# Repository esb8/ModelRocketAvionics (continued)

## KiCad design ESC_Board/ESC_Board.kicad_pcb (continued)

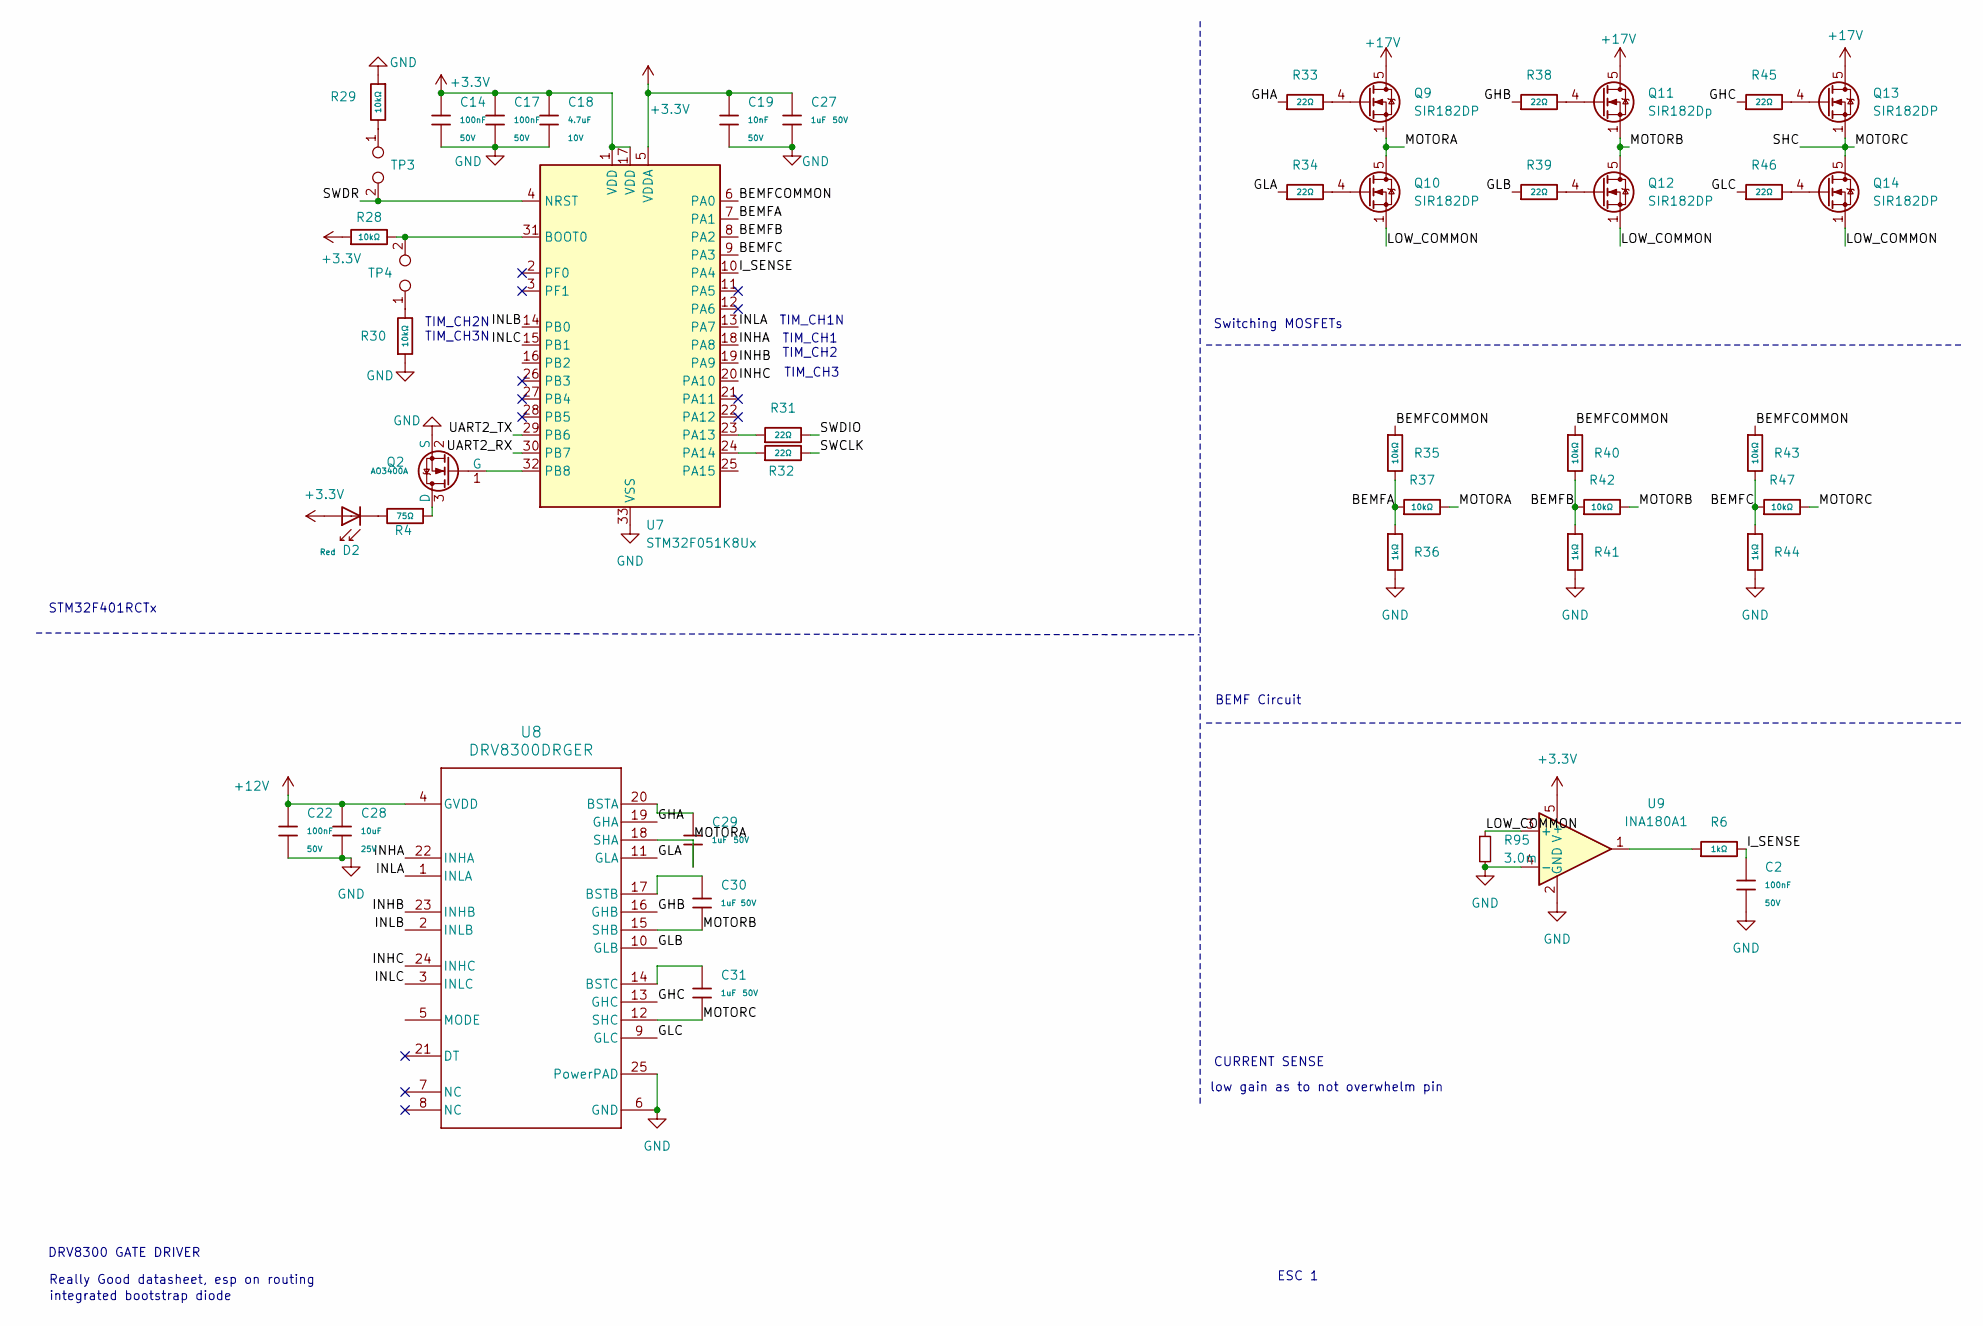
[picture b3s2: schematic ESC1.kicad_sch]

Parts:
C2, C14, C17, C22: 100nF; C_0402; Voltage Rated 50V; Tolerance ±10%; Part CL05B104KB54PNC; LCSC C307331
C18: 4.7uF; C_0402; Voltage Rated 10V; Tolerance ±20%; Part CL05A475MP5NRNC; LCSC C23733
C19: 10nF; C_0402; Voltage Rated 50V; Tolerance ±10%; Part CL05B103KB5NNNC; LCSC C15195
C27, C29, C30, C31: 1uF; C_0603; Voltage Rated 50V; Tolerance ±10%; LCSC C6119857
C28: 10uF; C_0603; Voltage Rated 25V; Tolerance ±20%; Part CL10A106MA8NRNC; LCSC C96446
D2: Red; D_0805; Forward Voltage (VF) 1.6V~2.6V; Part NCD0805R1; LCSC C84256
Q2: AO3400A; Q_SOT-23; Part AO3400A; LCSC C20917
Q9, Q10, Q12, Q13, Q14: SIR182DP; TDSON-8-1; LCSC C151507
Q11: SIR182Dp; TDSON-8-1; LCSC C151507
R4: 75Ω; R_0402; Tolerance ±1%; Part 0402WGF750JTCE; LCSC C4275
R6, R36, R41, R44: 1kΩ; R_0402; Tolerance ±1%; Part HP02WAJ0102TCE; LCSC C2759467
R28, R29, R30, R35, R37, R40, R42, R43, R47: 10kΩ; R_0402; Tolerance ±1%; LCSC C191123
R31, R32, R33, R34, R38, R39, R45, R46: 22Ω; R_0402; Tolerance ±1%; LCSC C400511
R95: 3.0m; R_2512_6332Metric; LCSC C2994640
TP3, TP4: TestPoint_2Pole
U7: STM32F051K8Ux; QFN-32-1EP_5x5mm_P0.5mm_EP3.45x3.45mm
U8: DRV8300DRGER; RGE0024B-IPC_A
U9: INA180A1; SOT-23-5

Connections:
+3.3V: C14.1, C17.1, C18.1, C19.1, C27.1, D2.2, R28.1, U7.1 (VDD), U7.5 (VDDA), U7.17 (VDD), U9.5 (V+); also elsewhere on the board
+12V: C22.1, C28.2, U8.4 (GVDD); also elsewhere on the board
+17V: Q9.5 (D), Q11.5 (D), Q13.5 (D); also elsewhere on the board
/ESC2.sch/BEMFA: R35.2, R36.1, R37.1, U7.7 (PA1)
/ESC2.sch/BEMFB: R40.2, R41.1, R42.1, U7.8 (PA2)
/ESC2.sch/BEMFC: R43.2, R44.1, R47.1, U7.9 (PA3)
/ESC2.sch/BEMFCOMMON: R35.1, R40.1, R43.1, U7.6 (PA0)
/ESC2.sch/GHA: R33.1, U8.19 (GHA)
/ESC2.sch/GHB: R38.1, U8.16 (GHB)
/ESC2.sch/GHC: R45.1, U8.13 (GHC)
/ESC2.sch/GLA: R34.1, U8.11 (GLA)
/ESC2.sch/GLB: R39.1, U8.10 (GLB)
/ESC2.sch/GLC: R46.1, U8.9 (GLC)
/ESC2.sch/INHA: U7.18 (PA8), U8.22 (INHA)
/ESC2.sch/INHB: U7.19 (PA9), U8.23 (INHB)
/ESC2.sch/INHC: U7.20 (PA10), U8.24 (INHC)
/ESC2.sch/INLA: U7.13 (PA7), U8.1 (INLA)
/ESC2.sch/INLB: U7.14 (PB0), U8.2 (INLB)
/ESC2.sch/INLC: U7.15 (PB1), U8.3 (INLC)
/ESC2.sch/I_SENSE: C2.1, R6.2, U7.10 (PA4)
/ESC2.sch/LOW_COMMON: Q10.1 (S), Q10.2 (S), Q10.3 (S), Q12.1 (S), Q12.2 (S), Q12.3 (S), Q14.1 (S), Q14.2 (S), Q14.3 (S), R95.1, U9.3 (+)
/ESC2.sch/MOTORA: C29.2, Q9.1 (S), Q9.2 (S), Q9.3 (S), Q10.5 (D), R37.2, U8.18 (SHA)
/ESC2.sch/MOTORB: C30.2, Q11.1 (S), Q11.2 (S), Q11.3 (S), Q12.5 (D), R42.2, U8.15 (SHB)
/ESC2.sch/MOTORC: C31.2, Q13.1 (S), Q13.2 (S), Q13.3 (S), Q14.5 (D), R47.2, U8.12 (SHC)
/ESC2.sch/SWCLK: R32.2
/ESC2.sch/SWDIO: R31.2
/ESC2.sch/SWDR: U7.4 (NRST)
/ESC2.sch/UART2_RX: U7.30 (PB7)
/ESC2.sch/UART2_TX: U7.29 (PB6)
GND: C2.2, C14.2, C17.2, C18.2, C19.2, C22.2, C27.2, C28.1, Q2.2 (S), R29.1, R30.1, R36.2, R41.2, R44.2, R95.2, U7.33 (VSS), U8.6 (GND), U8.25 (PowerPAD), U9.2 (GND), U9.4 (-); also elsewhere on the board
unnamed: D2.1, R4.2
unnamed: Q2.3 (D), R4.1
unnamed: Q2.1 (G), U7.32 (PB8)
unnamed: Q9.4 (G), R33.2
unnamed: Q10.4 (G), R34.2
unnamed: Q11.4 (G), R38.2
unnamed: Q12.4 (G), R39.2
unnamed: Q13.4 (G), R45.2
unnamed: Q14.4 (G), R46.2
unnamed: R6.1, U9.1
unnamed: R28.2, U7.31 (BOOT0)
unnamed: R31.1, U7.23 (PA13)
unnamed: R32.1, U7.24 (PA14)
unnamed: C29.1, U8.20 (BSTA)
unnamed: C30.1, U8.17 (BSTB)
unnamed: C31.1, U8.14 (BSTC)

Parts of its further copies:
C3, C4, C32, C34, C35, C42, C44, C45: 100nF; C_0402; Voltage Rated 50V; Tolerance ±10%; Part CL05B104KB54PNC; LCSC C307331
C33, C43: 10uF; C_0603; Voltage Rated 25V; Tolerance ±20%; Part CL10A106MA8NRNC; LCSC C96446
C36, C46: 4.7uF; C_0402; Voltage Rated 10V; Tolerance ±20%; Part CL05A475MP5NRNC; LCSC C23733
C37, C38, C39, C41, C47, C48, C49, C51: 1uF; C_0603; Voltage Rated 50V; Tolerance ±10%; LCSC C6119857
C40, C50: 10nF; C_0402; Voltage Rated 50V; Tolerance ±10%; Part CL05B103KB5NNNC; LCSC C15195
D4, D5: Red; D_0805; Forward Voltage (VF) 1.6V~2.6V; Part NCD0805R1; LCSC C84256
Q15, Q22: AO3400A; Q_SOT-23; Part AO3400A; LCSC C20917
Q16, Q17, Q19, Q20, Q21, Q23, Q24, Q26, Q27, Q28: SIR182DP; TDSON-8-1; LCSC C151507
Q18, Q25: SIR182Dp; TDSON-8-1; LCSC C151507
R48, R49, R50, R56, R58, R62, R64, R66, R70, R71, R72, R73, R79, R81, R85, R87, R89, R93: 10kΩ; R_0402; Tolerance ±1%; LCSC C191123
R51, R74: 75Ω; R_0402; Tolerance ±1%; Part 0402WGF750JTCE; LCSC C4275
R52, R53, R54, R55, R60, R61, R68, R69, R75, R76, R77, R78, R83, R84, R91, R92: 22Ω; R_0402; Tolerance ±1%; LCSC C400511
R57, R63, R65, R67, R80, R86, R88, R90: 1kΩ; R_0402; Tolerance ±1%; Part HP02WAJ0102TCE; LCSC C2759467
R96, R97: 3.0m; R_2512_6332Metric; LCSC C2994640
U10, U13: DRV8300DRGER; RGE0024B-IPC_A
U11, U14: STM32F051K8Ux; QFN-32-1EP_5x5mm_P0.5mm_EP3.45x3.45mm
U12, U15: INA180A1; SOT-23-5

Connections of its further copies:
+3.3V: C34.1, C35.1, C36.1, C40.1, C41.1, C44.1, C45.1, C46.1, C50.1, C51.1, D4.2, D5.2, R48.1, R71.1, U11.1 (VDD), U11.5 (VDDA), U11.17 (VDD), U12.5 (V+), U14.1 (VDD), U14.5 (VDDA), U14.17 (VDD), U15.5 (V+); also elsewhere on the board
+12V: C32.1, C33.2, C42.1, C43.2, U10.4 (GVDD), U13.4 (GVDD); also elsewhere on the board
+17V: Q16.5 (D), Q18.5 (D), Q20.5 (D), Q23.5 (D), Q25.5 (D), Q27.5 (D); also elsewhere on the board
/ESC3.sch1/BEMFA: R56.2, R57.1, R58.1, U11.7 (PA1)
/ESC3.sch1/BEMFB: R62.2, R63.1, R64.1, U11.8 (PA2)
/ESC3.sch1/BEMFC: R66.2, R67.1, R70.1, U11.9 (PA3)
/ESC3.sch1/BEMFCOMMON: R56.1, R62.1, R66.1, U11.6 (PA0)
/ESC3.sch1/GHA: R54.1, U10.19 (GHA)
/ESC3.sch1/GHB: R60.1, U10.16 (GHB)
/ESC3.sch1/GHC: R68.1, U10.13 (GHC)
/ESC3.sch1/GLA: R55.1, U10.11 (GLA)
/ESC3.sch1/GLB: R61.1, U10.10 (GLB)
/ESC3.sch1/GLC: R69.1, U10.9 (GLC)
/ESC3.sch1/INHA: U10.22 (INHA), U11.18 (PA8)
/ESC3.sch1/INHB: U10.23 (INHB), U11.19 (PA9)
/ESC3.sch1/INHC: U10.24 (INHC), U11.20 (PA10)
/ESC3.sch1/INLA: U10.1 (INLA), U11.13 (PA7)
/ESC3.sch1/INLB: U10.2 (INLB), U11.14 (PB0)
/ESC3.sch1/INLC: U10.3 (INLC), U11.15 (PB1)
/ESC3.sch1/I_SENSE: C3.1, R65.2, U11.10 (PA4)
/ESC3.sch1/LOW_COMMON: Q17.1 (S), Q17.2 (S), Q17.3 (S), Q19.1 (S), Q19.2 (S), Q19.3 (S), Q21.1 (S), Q21.2 (S), Q21.3 (S), R96.1, U12.3 (+)
/ESC3.sch1/MOTORA: C37.2, Q16.1 (S), Q16.2 (S), Q16.3 (S), Q17.5 (D), R58.2, U10.18 (SHA)
/ESC3.sch1/MOTORB: C38.2, Q18.1 (S), Q18.2 (S), Q18.3 (S), Q19.5 (D), R64.2, U10.15 (SHB)
/ESC3.sch1/MOTORC: C39.2, Q20.1 (S), Q20.2 (S), Q20.3 (S), Q21.5 (D), R70.2, U10.12 (SHC)
/ESC3.sch1/SWCLK: R53.2
/ESC3.sch1/SWDIO: R52.2
/ESC3.sch1/SWDR: U11.4 (NRST)
/ESC3.sch1/UART2_RX: U11.30 (PB7)
/ESC3.sch1/UART2_TX: U11.29 (PB6)
/ESC4.sch2/BEMFA: R79.2, R80.1, R81.1, U14.7 (PA1)
/ESC4.sch2/BEMFB: R85.2, R86.1, R87.1, U14.8 (PA2)
/ESC4.sch2/BEMFC: R89.2, R90.1, R93.1, U14.9 (PA3)
/ESC4.sch2/BEMFCOMMON: R79.1, R85.1, R89.1, U14.6 (PA0)
/ESC4.sch2/GHA: R77.1, U13.19 (GHA)
/ESC4.sch2/GHB: R83.1, U13.16 (GHB)
/ESC4.sch2/GHC: R91.1, U13.13 (GHC)
/ESC4.sch2/GLA: R78.1, U13.11 (GLA)
/ESC4.sch2/GLB: R84.1, U13.10 (GLB)
/ESC4.sch2/GLC: R92.1, U13.9 (GLC)
/ESC4.sch2/INHA: U13.22 (INHA), U14.18 (PA8)
/ESC4.sch2/INHB: U13.23 (INHB), U14.19 (PA9)
/ESC4.sch2/INHC: U13.24 (INHC), U14.20 (PA10)
/ESC4.sch2/INLA: U13.1 (INLA), U14.13 (PA7)
/ESC4.sch2/INLB: U13.2 (INLB), U14.14 (PB0)
/ESC4.sch2/INLC: U13.3 (INLC), U14.15 (PB1)
/ESC4.sch2/I_SENSE: C4.1, R88.2, U14.10 (PA4)
/ESC4.sch2/LOW_COMMON: Q24.1 (S), Q24.2 (S), Q24.3 (S), Q26.1 (S), Q26.2 (S), Q26.3 (S), Q28.1 (S), Q28.2 (S), Q28.3 (S), R97.1, U15.3 (+)
/ESC4.sch2/MOTORA: C47.2, Q23.1 (S), Q23.2 (S), Q23.3 (S), Q24.5 (D), R81.2, U13.18 (SHA)
/ESC4.sch2/MOTORB: C48.2, Q25.1 (S), Q25.2 (S), Q25.3 (S), Q26.5 (D), R87.2, U13.15 (SHB)
/ESC4.sch2/MOTORC: C49.2, Q27.1 (S), Q27.2 (S), Q27.3 (S), Q28.5 (D), R93.2, U13.12 (SHC)
/ESC4.sch2/SWCLK: R76.2
/ESC4.sch2/SWDIO: R75.2
/ESC4.sch2/SWDR: U14.4 (NRST)
/ESC4.sch2/UART2_RX: U14.30 (PB7)
/ESC4.sch2/UART2_TX: U14.29 (PB6)
GND: C3.2, C4.2, C32.2, C33.1, C34.2, C35.2, C36.2, C40.2, C41.2, C42.2, C43.1, C44.2, C45.2, C46.2, C50.2, C51.2, Q15.2 (S), Q22.2 (S), R49.1, R50.1, R57.2, R63.2, R67.2, R72.1, R73.1, R80.2, R86.2, R90.2, R96.2, R97.2, U10.6 (GND), U10.25 (PowerPAD), U11.33 (VSS), U12.2 (GND), U12.4 (-), U13.6 (GND), U13.25 (PowerPAD), U14.33 (VSS), U15.2 (GND), U15.4 (-); also elsewhere on the board
unnamed: D4.1, R51.2
unnamed: D5.1, R74.2
unnamed: Q15.3 (D), R51.1
unnamed: Q15.1 (G), U11.32 (PB8)
unnamed: Q16.4 (G), R54.2
unnamed: Q17.4 (G), R55.2
unnamed: Q18.4 (G), R60.2
unnamed: Q19.4 (G), R61.2
unnamed: Q20.4 (G), R68.2
unnamed: Q21.4 (G), R69.2
unnamed: Q22.3 (D), R74.1
unnamed: Q22.1 (G), U14.32 (PB8)
unnamed: Q23.4 (G), R77.2
unnamed: Q24.4 (G), R78.2
unnamed: Q25.4 (G), R83.2
unnamed: Q26.4 (G), R84.2
unnamed: Q27.4 (G), R91.2
unnamed: Q28.4 (G), R92.2
unnamed: R65.1, U12.1
unnamed: R88.1, U15.1
unnamed: C37.1, U10.20 (BSTA)
unnamed: C38.1, U10.17 (BSTB)
unnamed: C39.1, U10.14 (BSTC)
unnamed: R48.2, U11.31 (BOOT0)
unnamed: R52.1, U11.23 (PA13)
unnamed: R53.1, U11.24 (PA14)
unnamed: C47.1, U13.20 (BSTA)
unnamed: C48.1, U13.17 (BSTB)
unnamed: C49.1, U13.14 (BSTC)
unnamed: R71.2, U14.31 (BOOT0)
unnamed: R75.1, U14.23 (PA13)
unnamed: R76.1, U14.24 (PA14)

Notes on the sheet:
DRV8300 GATE DRIVER
TIM_CH3
TIM_CH1N
low gain as to not overwhelm pin
Switching MOSFETs
CURRENT SENSE
integrated bootstrap diode
TIM_CH3N
BEMF Circuit
STM32F401RCTx
TIM_CH2
ESC 1
TIM_CH1
TIM_CH2N
Really Good datasheet, esp on routing

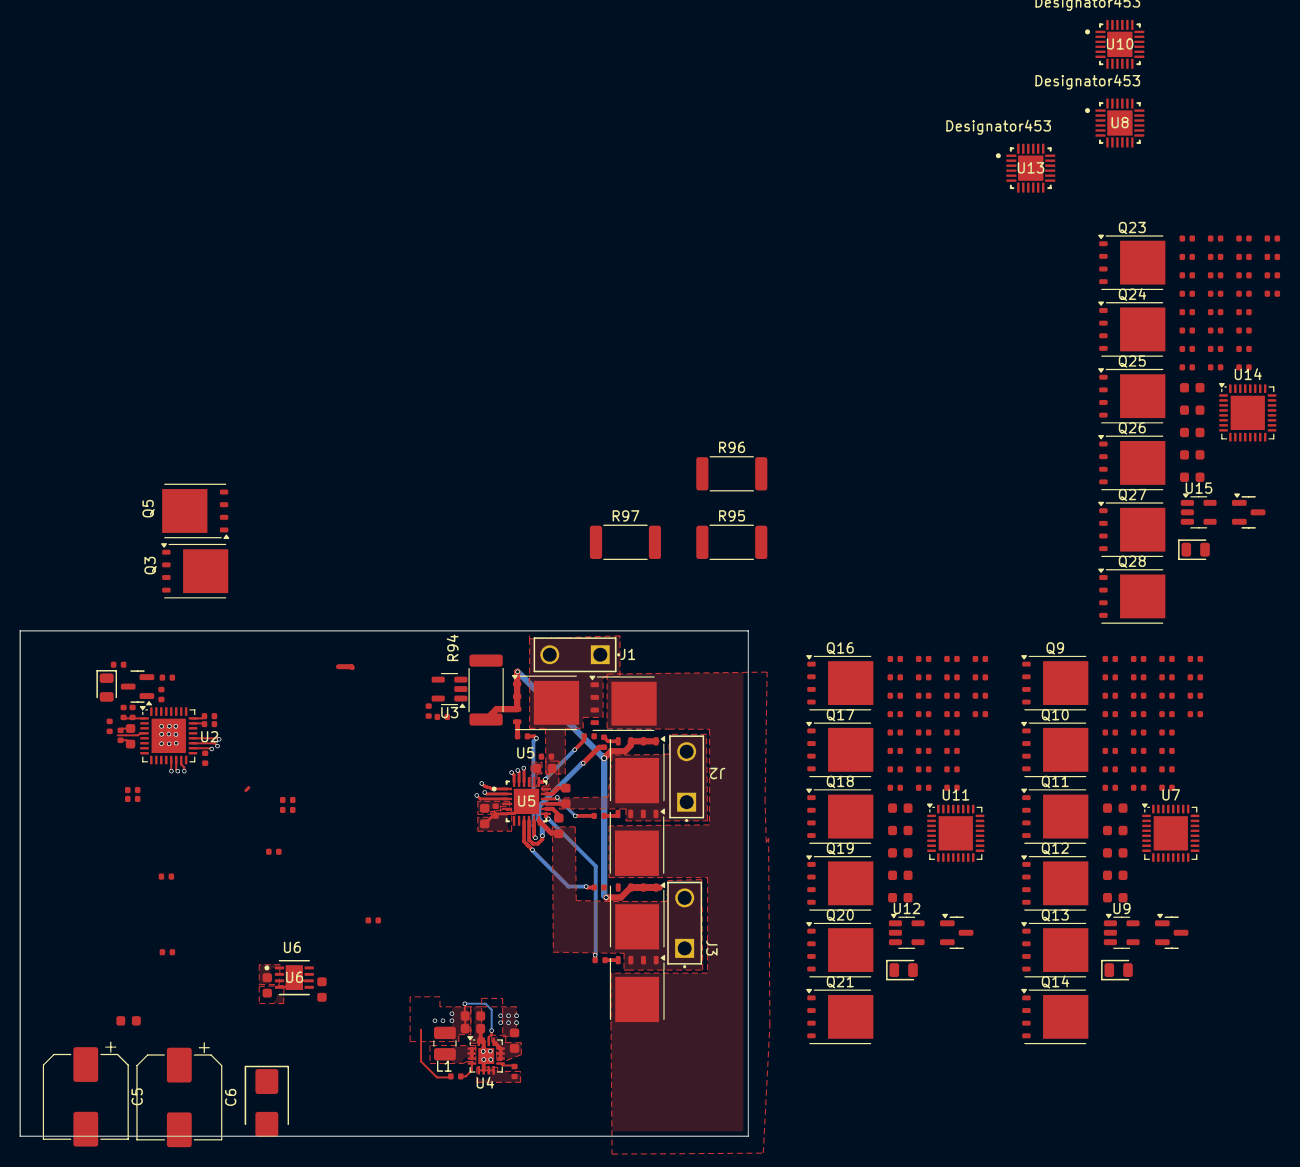
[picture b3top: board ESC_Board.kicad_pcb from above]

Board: 4 copper layers, 73.2 x 50.8 mm, 199 parts (0 on the bottom side), 155 nets.

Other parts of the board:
Q3#2, Q5#2: SIR182DP; TDSON-8-1

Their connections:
+17V: Q5#2.5 (D); also elsewhere on the board
/LOW_COMMON: Q3#2.1 (S), Q3#2.2 (S), Q3#2.3 (S); also elsewhere on the board
/MOTORA: Q3#2.5 (D), Q5#2.1 (S), Q5#2.2 (S), Q5#2.3 (S); also elsewhere on the board
unnamed 119: Q3#2.4 (G); also elsewhere on the board
unnamed 121: Q5#2.4 (G); also elsewhere on the board

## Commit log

2025-03-31 V0.1 Schematic
2025-04-01 Changed I2C to SPI (4Wire) switched IMU, need to add decoupling capacitors and fix GPS
2025-04-01 commit corrected files
2025-04-02 Added Capacitors
2025-04-05 outlining
2025-04-05 testing webhooks
2025-04-05 testing webhooks #2
2025-04-06 push power system MP2307DN
2025-04-06 Added Buck Converter
2025-04-07 Finalized sensor board schematic
2025-04-07 removed locked file
2025-04-07 Added basic components
2025-04-07 Added active components
2025-04-25 Updated GPS and Buck Converter
2025-04-28 Changed MCU to be compatible with AM32, added Half Bridge driver and sensor circuitry
2025-05-03 Started PCB Design
2025-05-18 Updated STM32 and overhauled SPI wiring, added external flash memory, added LoRa Transciever, moved buck converter to ESC-Board which will handle power distrubution, signficant progress on PCB design.
2025-05-20 Finalized PCB Design
2025-05-20 Added 3D Models, Changes to Copper Zone, Added Crystal Oscillator to PCB.
2025-05-26 added mounting holes
2025-05-26 Added LCSC Part Numbers
2025-05-26 Updated DRC requirements, footprints, and board stackup for impedance management
2025-06-29 added pull-up resistors, added keepout zones.
2025-07-04 Fixed GPS wiring
2025-07-10 DroneController: Improved clarity of silkscreen and added manual reset test pad for the MCU.
    ESC Board: Modified Buck Converter, added SWD debugging, added ICs for BLDC control
2025-07-11 ESC Board: added mosfets and BackEMF circuitry
2025-07-13 ESC Board: Finalized ESC design
2025-07-15 Began PCB design
2025-07-15 Added UART debugging for DroneController, repecced crystal oscillator.
2025-07-17 DroneController: Adjusted crystal oscillator, added SWD debugging
2025-07-19 Fixed wiring, Added pull-up on CS, respecced IMU, began work on a new layout
2025-07-20 Finalized PCB and layout of MKII of Drone Controller
2025-07-21 Finalized MK II of drone controller, added 3D models, followed PCBWay DRC.
2025-07-22 Cleaned up repo directory.
2025-07-22 Basic layout and routing, modified schematic, and directory
2025-07-29 Added more room for antenna pin on LoRa
2025-08-05 Added RP2040 compatible branch, addded battery protection circuitry
2025-08-06 Overhauled layout, added more clearance for antenna.
2025-08-07 Fixed layout of Schematic and pin labelling.
